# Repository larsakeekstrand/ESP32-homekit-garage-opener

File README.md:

# ESP32 Homekit garage door opener
## Introduction
This is a homekit garage opener for the ESP32. It's a bit a work in progress, but it should mostly work.

Features:
* Controls a relay that opens/closes the door.
* Uses a reed sensor to detect if the door is open/closed.
* Contains a DHT22 temperature/humidity sensor.
* Auto-close timer (default 10 min, configurable, 0 = off).
* Door-left-open HomeKit alert via a Contact Sensor accessory.
* Vacation/lockout switch to refuse all open and close commands.
* Local status and configuration web page at `http://<device-ip>:8080/`.

Schematics for the hardware are in [docs/Schematic_GarageOpener.pdf](docs/Schematic_GarageOpener.pdf), drawn in [KiCad](https://www.kicad.org/) — the project (rev 1 carrier PCB for an ESP32 DevKitC V4) is in [hardware/garage-opener-pcb](hardware/garage-opener-pcb), with a bill of materials in [docs/BOM_GarageOpener.pdf](docs/BOM_GarageOpener.pdf). The routed board ([render](docs/PCB_GarageOpener_3d.png)) and Aisler-ready Gerbers are in [hardware/garage-opener-pcb/fab](hardware/garage-opener-pcb/fab), and a 3D-printable wall-mounted enclosure for it is in [hardware/enclosure](hardware/enclosure/README.md).

The STL files below are for the original hand-wired prototype housing.

STL files for the housing can be found [here](https://github.com/larsakeekstrand/ESP32-homekit-garage-opener/blob/2dc0cb2f88ffee0f719a3f48c10d991301077dc2/docs/GarageOpenerTop.stl), [here](https://github.com/larsakeekstrand/ESP32-homekit-garage-opener/blob/2dc0cb2f88ffee0f719a3f48c10d991301077dc2/docs/GarageOpenerBottom.stl) and [here](https://github.com/larsakeekstrand/ESP32-homekit-garage-opener/blob/d89407ebe4e6d4afd1c8a517a600cc80013ba3aa/docs/GarageOpenerBottomButton.stl).

An overview of how to assemble the housing can be found [here](https://github.com/larsakeekstrand/ESP32-homekit-garage-opener/blob/d89407ebe4e6d4afd1c8a517a600cc80013ba3aa/docs/GarageOpenerCompleteNotPrintable.stl).

## Safety features

### Auto-close timer

When the door has been open for more than **10 minutes** (default), the firmware automatically
sends a close command. The timeout is configurable on the local web page (see below); set it to
`0` to disable auto-close entirely.

### Door-left-open alert

A HomeKit **Contact Sensor** named **"Garage Left Open"** fires when the door has been open for
more than **5 minutes** (default). Enable notifications on it in the Home app to receive an alert.
Set the threshold to `0` on the web page to disable the alert. The sensor still reports even when
the lockout switch is ON.

### Vacation / lockout switch

A HomeKit **Switch** named **"Lockout"** puts the opener into an absolute freeze: while it is ON,
HomeKit open and close commands are refused and the auto-close timer is suspended. It can be
toggled from both the Home app and the local web page — they stay in sync.

### Local status and configuration web page

The device serves a status and config page at `http://<device-ip>:8080/` on the local network (plain
HTTP, no HTTPS, LAN only). Port **8080** is used because the HomeKit (HAP) server already occupies
port 80. Find the device's IP from your router, or via mDNS — it advertises over Bonjour, e.g.
`dns-sd -B _hap._tcp` shows it as `GarageOpener-XXXXXX`.

**First-time setup — set a password promptly.** On the very first visit the device has no password
and shows a one-time "create password" screen (trust-on-first-use). Anyone on the same LAN can set
the password until you do, so set it immediately after first access. The firmware-flash endpoint
(`POST /api/ota`) is equally open during this window — since it can replace the running firmware,
set the password promptly, especially on an untrusted LAN (uploaded images are validated against the
`garage` app descriptor and the endpoint is LAN-only, but the credential gate is the main barrier).

After the password is set, the page requires **HTTP Basic Auth** (username `admin`, your chosen
password). From there you can:

* View live status: door state, lockout, Wi-Fi RSSI, temperature, humidity, uptime.
* View system info: firmware version, free heap, MAC address, IP address, reset reason.
* View persisted counters: door cycles, auto-closes, door-left-open trips, faults.
* Edit the auto-close timeout, door-left-open threshold, **OTA poll interval** (5–1440 min),
  **door-move timeout** (3–30 s), and **relay pulse length** (100–2000 ms). All settings persist
  in NVS. The OTA poll interval takes effect within ~10 s — no reboot needed.
* Trigger an immediate GitHub version check with **Check for updates now** (no effect while
  auto-updates are paused — resume first).
* Restart the device with **Reboot device** (asks for confirmation; HomeKit and the web page drop
  for ~15 s while it boots).
* Change the admin password.
* Reset a latched auto-close fault (see below).

**Editing the web page source.** The page HTML and JavaScript live in `tools/web/page.html`
(main status/config page) and `tools/web/setup.html` (first-time password setup). After editing
either file, regenerate the embedded C string literals:

```bash
python3 tools/gen_web_page.py
```

This rewrites the relevant sections of `main/web_server.c`. Rebuild and flash as normal.
Edit only `tools/web/*.html` — the `PAGE_HTML` / `SETUP_HTML` C strings in `web_server.c` are
generated and will be silently overwritten by the next `gen_web_page.py` run.

### Auto-close fault detection

If the reed sensor remains stuck reporting "open" after a close command, the firmware makes at most
**3 attempts** then latches auto-close off, so it never oscillates the door. A minimum of 60
seconds between pulses and a per-hour cap serve as additional backstops.

The fault is surfaced three ways:

1. A banner on the local web page with a **Reset** button to clear it manually.
2. A HomeKit **StatusFault** indicator on the Garage Door Opener accessory.
3. A log message at error severity.

The fault clears automatically when the door genuinely reports closed, or immediately when you
press **Reset** on the web page.

### HomeKit caveat after updating

If you are updating from a firmware version that does not include these features, you may need to
**remove and re-add the accessory** in the Home app to make the new **"Garage Left Open"** Contact
Sensor and **"Lockout"** Switch tiles visible.

## Getting started
### Setup host environment

Set up the host environment and **Espressif ESP-IDF v5.5.2** using the instructions given [here](https://docs.espressif.com/projects/esp-idf/en/latest/get-started/index.html).

Set up the Espressif esp-homekit-sdk using the instructions given [here](https://github.com/espressif/esp-homekit-sdk).

The DHT22/AM2301 driver is fetched automatically by the **ESP Component Manager** (declared in `main/idf_component.yml`) — no separate clone of `esp-idf-lib` is required.

### Get ESP32-homekit-garage-opener

Clone this repository **alongside** (not inside) your `~/esp/` directory:

```
cd ~/source    # ~/source is a sibling of ~/esp
git clone https://github.com/larsakeekstrand/ESP32-homekit-garage-opener
```

After the installation the directory structure should look like this:

```
~/
  esp/
    esp-idf            # ESP-IDF v5.5.2
    esp-homekit-sdk    # Espressif HomeKit SDK (cloned peer)
  source/
    ESP32-homekit-garage-opener   # this repo
```

`CMakeLists.txt` locates `esp-homekit-sdk` at `../../esp/esp-homekit-sdk` relative to the repo root, or via the `HOMEKIT_PATH` environment variable.

### Configure
Source the ESP-IDF environment, then run `idf.py menuconfig` to set Wi-Fi credentials and the HomeKit setup code before flashing:
```bash
. ~/esp/esp-idf/export.sh
cd ~/source/ESP32-homekit-garage-opener
idf.py menuconfig
```

Set the Wi-Fi SSID and password under **App Wi-Fi configuration**. Set the HomeKit setup code and ID under **HAP Setup** (or leave the hardcoded defaults for development).

### Compile and Flash

```bash
idf.py set-target esp32
idf.py build
idf.py flash monitor
```

## Continuous Integration & Releases

### CI (automatic)

Every push to `main` and every pull request targeting `main` triggers the **Build** workflow
(`.github/workflows/build.yml`). It:

- Builds the firmware with ESP-IDF v5.5.2 and target `esp32`.
- Verifies the image fits the 1600 KB OTA partition.
- Uploads `garage.bin` as a downloadable artifact.

Warnings in the app sources are treated as errors (`-Werror`), so a warning will fail the build.

### Cutting a release (manual)

1. Go to the **Actions** tab in GitHub.
2. Select the **Release** workflow.
3. Click **Run workflow**, enter a version string (e.g. `1.1.0`, no leading `v`), and confirm.

The workflow builds with that version baked in as `FW_VERSION`, tags the commit `v1.1.0`, and
publishes a GitHub Release with two assets: `garage.bin` and `version.txt`.

### Self-updating OTA

The device checks `releases/latest` on GitHub **every hour** (default). If `version.txt` reports a
version newer than the running firmware, the device downloads `garage.bin` via HTTPS and reboots
into the new image. A bad image that never completes initialization is **automatically rolled back**
by the bootloader.

The poll interval and repo base URL are configurable via `idf.py menuconfig` →
**Example Configuration** → OTA options (`CONFIG_OTA_POLL_INTERVAL_SEC`,
`CONFIG_OTA_GITHUB_BASE_URL`).

> **Security note:** anyone who can publish a GitHub Release to this repo can push firmware to the
> device. Images are not cryptographically signed — acceptable for a personal repo.

### LAN push-OTA (forced / beta updates)

You can push a locally-built image directly to the device over the local network — useful for
testing a beta build without cutting a GitHub release.

**Build a versioned beta first.** A build with the default `FW_VERSION=0.0.0-dev` is treated as
*older* than the latest release by the hourly poller, so it would be reverted on the next poll.
Pass a real version to avoid that:

```bash
idf.py -DFW_VERSION=1.2.0-beta build
```

**Upload with `garage-push`.** The CLI lives at `tools/garage-push/` (Rust). Build and run it with
`cargo`:

```bash
cd tools/garage-push
cargo build                            # or: cargo run -- <subcommand>
```

Subcommands:

| Subcommand | What it does |
|------------|-------------|
| `push --host <ip> --file build/garage.bin` | Uploads the image to the device, waits for it to reboot into the new firmware |
| `resume --host <ip>` | Re-enables the hourly GitHub auto-update poller |
| `status --host <ip>` | Prints the device status JSON |

The `push` subcommand authenticates with HTTP Basic Auth (username `admin`, your web page password).
The password is resolved in order: `--password <pw>` flag → `$GARAGE_PASSWORD` environment variable
→ interactive prompt.

The device validates the uploaded image before flashing: it checks the app descriptor for the
correct project name and magic word. A wrong or corrupt image is rejected and the running firmware
is untouched. An image that does boot but then crashes or hangs is **automatically rolled back** by
the bootloader (same rollback mechanism as GitHub OTA).

**Auto-update pause.** A successful `push` automatically pauses the hourly GitHub poller; the pause
flag is stored in NVS and survives reboots. Consequently, if the pushed beta fails to boot and the
bootloader rolls back to the previous image, that restored image comes back with auto-updates still
paused — run `garage-push resume --host <ip>` (or toggle the web-page **Auto-update** switch) to
re-enable them. Re-enable auto-updates with:

```bash
cargo run -- resume --host <ip>
```

Or toggle the **Auto-update** switch on the local web page — it shows **on** or **PAUSED**.

### Wi-Fi credentials & OTA

Wi-Fi credentials are stored in the **`nvs` flash partition**, which OTA never touches (OTA only
rewrites the inactive app slot). So **credentials persist across updates** — you don't re-enter them
when the device self-updates.

The release images built by CI are **provisioning-mode** (no credentials baked in). Don't put your
SSID/password into the build or into GitHub — provision the device instead:

- **First-time / after a reset:** when the device is unprovisioned it advertises a BLE service named
  `PROV_XXYYZZ` (last 3 bytes of its MAC) and prints a **QR code + proof-of-possession (POP)** to the
  serial monitor. Install Espressif's **ESP BLE Provisioning** app (iOS/Android), scan the QR code
  (or pick `PROV_XXYYZZ` and enter the POP), choose your Wi-Fi, and enter the password. The creds are
  saved to NVS over an encrypted BLE link.
- **Re-provision:** short-press the boot/reset button (~3 s) to reset the network → the device
  re-advertises for provisioning. A long press (~10 s) is a full factory reset (also unpairs
  HomeKit).

> A locally-built **hardcoded** image (`menuconfig` → App Wi-Fi → *Use hardcoded credentials*) is fine
> for bench testing, but the first OTA replaces it with a provisioning image. Because esp-wifi caches
> the hardcoded credentials in NVS, the provisioning image reconnects using them — but from then on
> the device is provisioning-based, so re-provision over BLE if you ever clear the network config.

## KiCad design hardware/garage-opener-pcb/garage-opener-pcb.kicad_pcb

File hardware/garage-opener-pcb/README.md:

# Garage opener carrier PCB (rev 1)

KiCad 10 project for a carrier board that an **ESP32 DevKitC V4 (ESP32-WROOM-32U, 38-pin)** plugs
into. It adds a 5 V screw-terminal input (PTC fuse + Schottky), an on-board SRD-05VDC relay for the
opener's push-button input, a protected reed-switch input, an on-board DHT22, RUN/DOOR LEDs and two
board-ID straps. The GPIO map is identical to the prototype (`main/board.h`), so the same firmware
and OTA image run on both.

- Schematic: `garage-opener-pcb.kicad_sch` (PDF: `../../docs/Schematic_GarageOpener.pdf`)
- BOM: `bom.csv` (DNP parts excluded); printable version `../../docs/BOM_GarageOpener.pdf`,
  regenerated with `python3 make_bom_pdf.py` after re-exporting `bom.csv`. U1 is the devkit itself; its footprint needs two
  1x19 2.54 mm female headers, which are not a separate BOM line.
- Design + bring-up checklist: `../../docs/superpowers/specs/2026-10-16-carrier-pcb-schematic-design.md`

## Checking the schematic after edits

    python3 check_schematic.py

Exports the netlist with `kicad-cli` and checks every net, footprint, the DNP ID straps, and that
each GPIO in `main/board.h` lands on the right circuit. Run ERC too:

    kicad-cli sch erc --severity-all garage-opener-pcb.kicad_sch

Expected: 0 errors; 1 warning that the embedded `MMBT2222A` differs from the library copy (it is a
flattened derived symbol) is harmless.

## Before ordering a PCB

- Measure the devkit: rows must be 25.4 mm apart (footprint `garage-opener:ESP32-DevKitC-V4_Socket`).
- Power J1 from a **5.1–5.2 V** supply: the Schottky + PTC drop ~0.45 V, and the devkit's LDO needs ~4.3 V.
- Check whether the devkit has a diode on USB VBUS before using USB and J1 at the same time.
- Board ID rev 1 = `00` (R9, R11 fitted). Future revisions: fit R8 and/or R10 instead.
- J1–J3 are pluggable Phoenix-style headers. J1 (power) is 3.81 mm pitch and J2/J3 are 5.08 mm, so the
  power plug can't go into the reed socket.
- Relay contacts follow KiCad's SRD symbol (J2: 1 COM, 2 NO, 3 NC). On the first board, confirm
  with a meter that COM–NO is open while the relay is unpowered.

## PCB

Renders: `kicad-cli pcb render --side top ...` and `--perspective --rotate '-40,0,30'`. KiCad's stock LED
model is red (the BOM has green RUN / amber DOOR), U2 shows as a socket (the DHT22 is soldered flat), and
the devkit has no 3D model.

- `garage-opener-pcb.kicad_pcb` is the source of truth. `tools/layout.py`, `tools/route.py` and
  `tools/silk.py` built rev 1 from scratch. Layout refuses to overwrite without `--force`, which
  discards the routing. `route.py --refill-only` refills the GND pours and adds stitching vias.
- Check after any edit: `python3 check_pcb.py`. It checks placement, connector/USB orientation and
  the silkscreen labels, that the custom rules in `garage-opener-pcb.kicad_dru` load, DRC, unconnected
  items and schematic parity.
- Fab files: `sh fab.sh`, then upload `fab/garage-opener-pcb-gerbers.zip` to Aisler (2 layers,
  1.6 mm, HASL). Aisler also accepts the `.kicad_pcb` directly. `fab/` also has a STEP model and an STL;
  the enclosure scripts read the STL.
- The DHT22 is soldered **flat** (leads bent 90°, grille facing the lid) over the marked keep-out,
  not in a socket.
- Relay contact tracks are 1 mm wide with 2 mm clearance to everything else (net class `Contact`).
- Enclosure: `../enclosure/` (generated from this board; rerun its `export_board_dims.py` after moving parts).

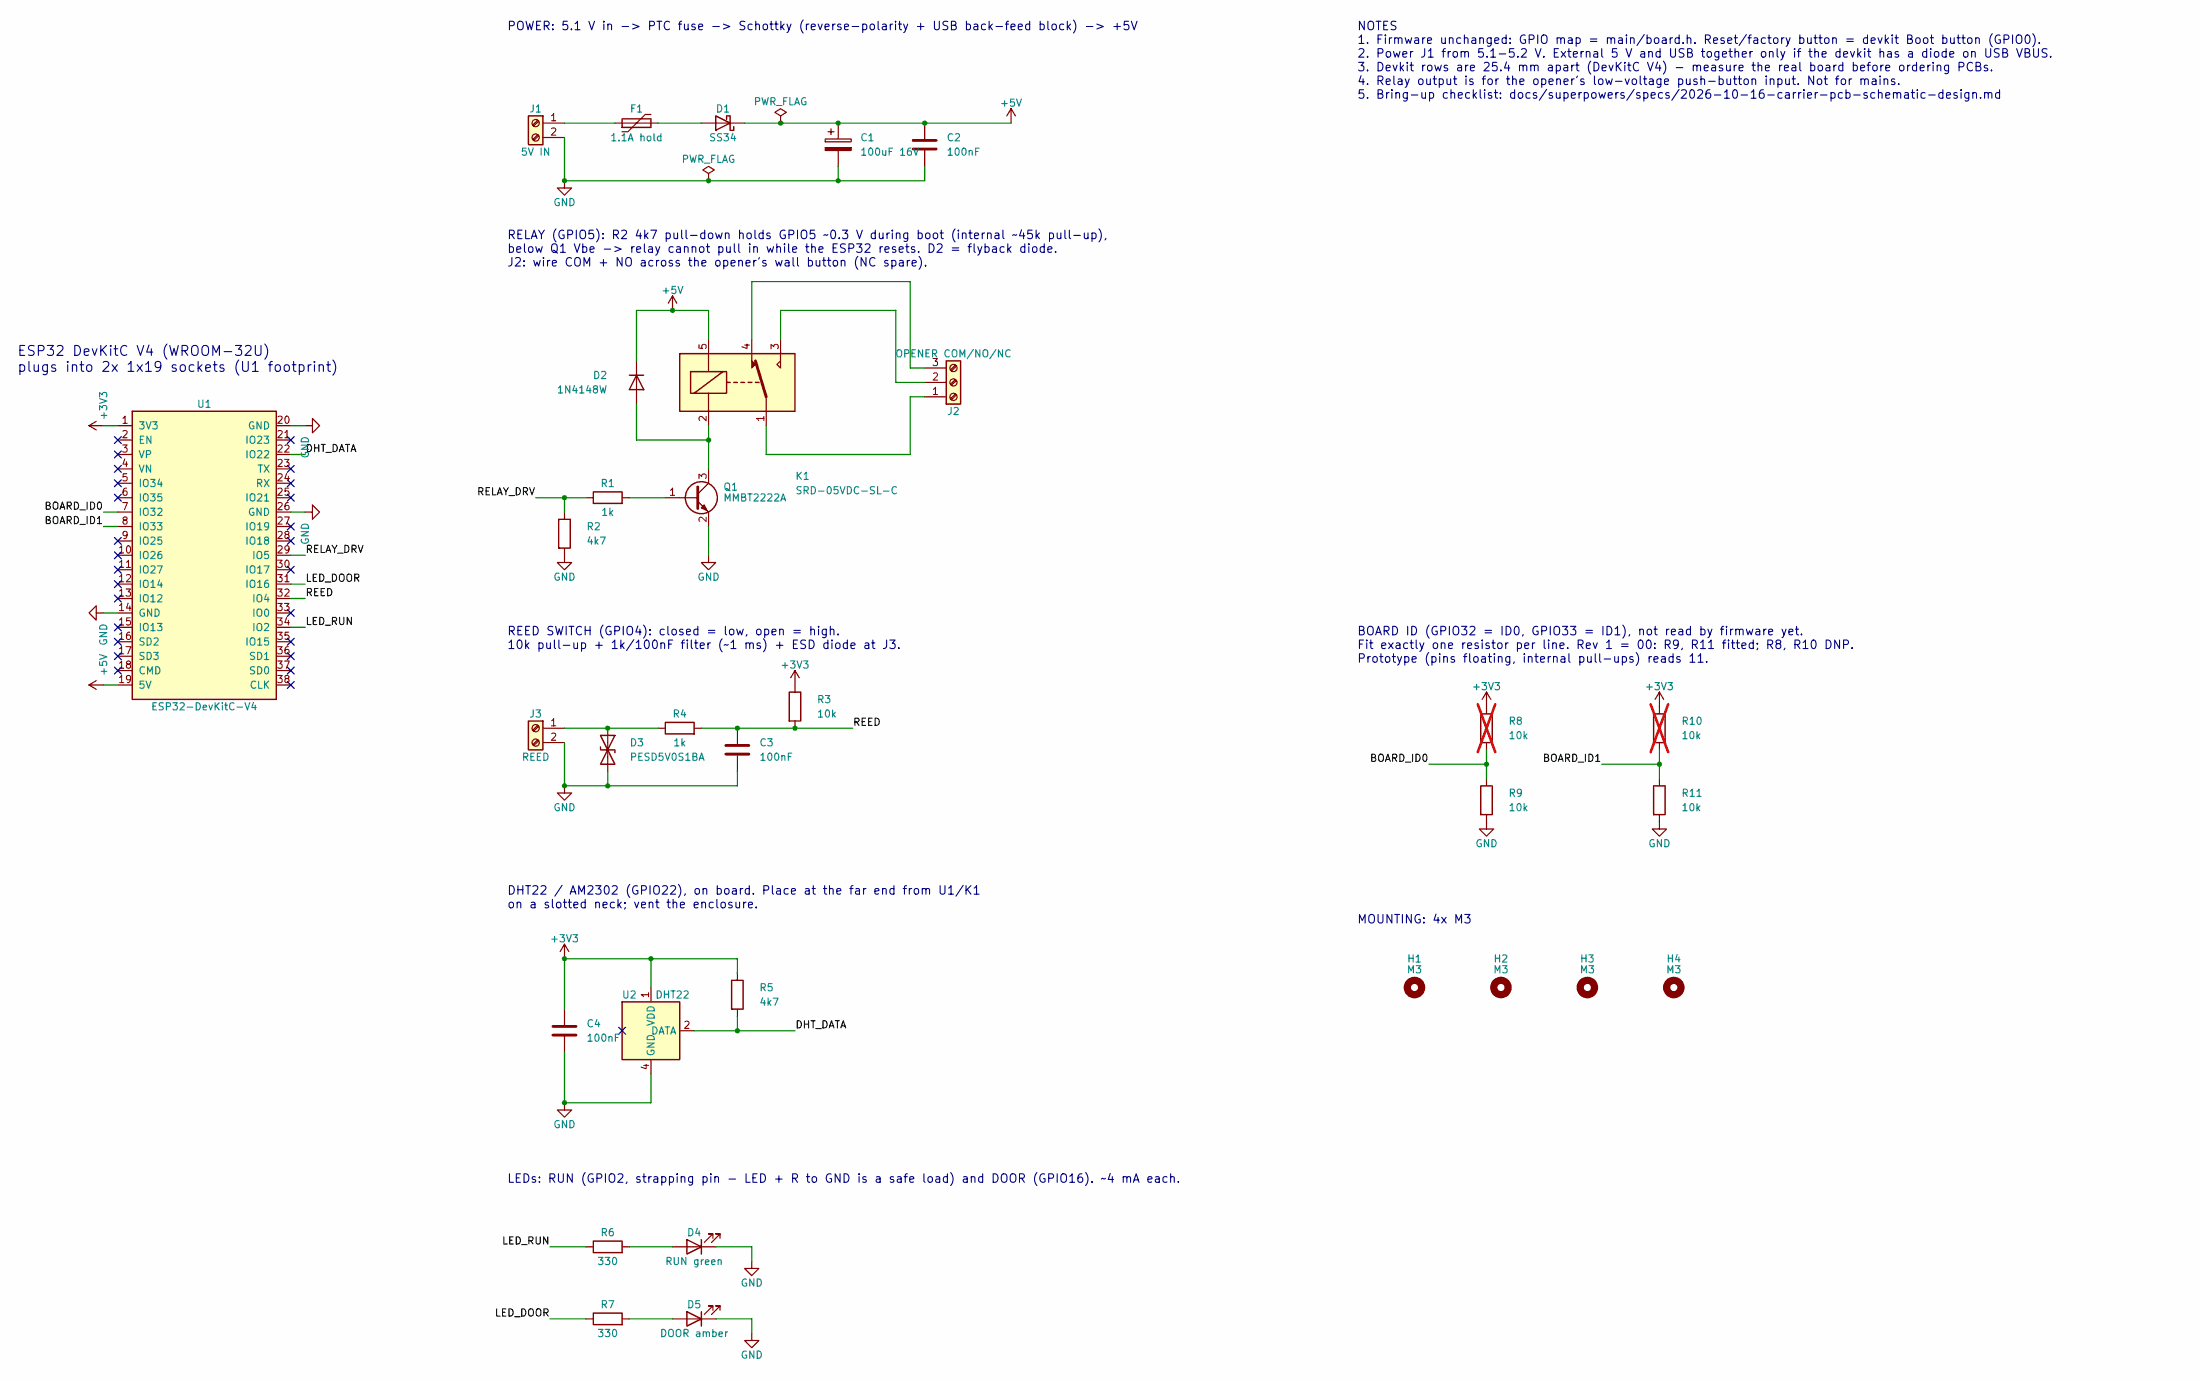
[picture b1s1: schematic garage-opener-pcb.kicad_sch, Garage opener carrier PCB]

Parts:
C1: 100uF 16V; CP_Radial_D6.3mm_P2.50mm
C2, C3, C4: 100nF; C_0805_2012Metric; LCSC C49678
D1: SS34; D_SMA; LCSC C8678
D2: 1N4148W; D_SOD-123; LCSC C81598
D3: PESD5V0S1BA; D_SOD-323
D4: RUN green; LED_D3.0mm
D5: DOOR amber; LED_D3.0mm
F1: 1.1A hold; Fuse_1812_4532Metric
H1, H2, H3, H4: M3; MountingHole_3.2mm_M3
J1: 5V IN; PhoenixContact_MC_1,5_2-G-3.81_1x02_P3.81mm_Horizontal
J2: OPENER COM/NO/NC; PhoenixContact_MSTBA_2,5_3-G-5,08_1x03_P5.08mm_Horizontal
J3: REED; PhoenixContact_MSTBA_2,5_2-G-5,08_1x02_P5.08mm_Horizontal
K1: SRD-05VDC-SL-C; Relay_SPDT_SANYOU_SRD_Series_Form_C; LCSC C35449
Q1: MMBT2222A; SOT-23
R1, R4: 1k; R_0805_2012Metric; LCSC C17513
R2, R5: 4k7; R_0805_2012Metric; LCSC C17673
R3, R9, R11: 10k; R_0805_2012Metric; LCSC C17414
R6, R7: 330; R_0805_2012Metric; LCSC C17630
R8, R10: 10k; R_0805_2012Metric; LCSC C17414; not fitted
U1: ESP32-DevKitC-V4; ESP32-DevKitC-V4_Socket
U2: DHT22; PinSocket_1x04_P2.54mm_Vertical

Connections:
+3V3: C4.1, R3.1, R5.1, R8.1, R10.1, U1.1 (3V3), U2.1 (VDD)
+5V: C1.1, C2.1, D1.1 (K), D2.1 (K), K1.5, U1.19 (5V)
/BOARD_ID0: R8.2, R9.1, U1.7 (IO32)
/BOARD_ID1: R10.2, R11.1, U1.8 (IO33)
/DHT_DATA: R5.2, U1.22 (IO22), U2.2 (DATA)
/LED_DOOR: R7.1, U1.31 (IO16)
/LED_RUN: R6.1, U1.34 (IO2)
/REED: C3.1, R3.2, R4.2, U1.32 (IO4)
/RELAY_DRV: R1.1, R2.1, U1.29 (IO5)
GND: C1.2, C2.2, C3.2, C4.2, D3.2 (A2), D4.1 (K), D5.1 (K), J1.2, J3.2, Q1.2 (E), R2.2, R9.2, R11.2, U1.14 (GND), U1.20 (GND), U1.26 (GND), U2.4 (GND)
unnamed: D1.2 (A), F1.2
unnamed: D2.2 (A), K1.2, Q1.3 (C)
unnamed: D3.1 (A1), J3.1, R4.1
unnamed: D4.2 (A), R6.2
unnamed: D5.2 (A), R7.2
unnamed: F1.1, J1.1
unnamed: J2.1, K1.1
unnamed: J2.2, K1.3
unnamed: J2.3, K1.4
unnamed: Q1.1 (B), R1.2

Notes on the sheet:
BOARD ID (GPIO32 = ID0, GPIO33 = ID1), not read by firmware yet. Fit exactly one resistor per line. Rev 1 = 00: R9, R11 fitted; R8, R10 DNP. Prototype (pins floating, internal pull-ups) reads 11.
LEDs: RUN (GPIO2, strapping pin - LED + R to GND is a safe load) and DOOR (GPIO16). ~4 mA each.
DHT22 / AM2302 (GPIO22), on board. Place at the far end from U1/K1 on a slotted neck; vent the enclosure.
REED SWITCH (GPIO4): closed = low, open = high. 10k pull-up + 1k/100nF filter (~1 ms) + ESD diode at J3.
ESP32 DevKitC V4 (WROOM-32U) plugs into 2x 1x19 sockets (U1 footprint)
MOUNTING: 4x M3
NOTES 1. Firmware unchanged: GPIO map = main/board.h. Reset/factory button = devkit Boot button (GPIO0). 2. Power J1 from 5.1-5.2 V. External 5 V and USB together only if the devkit has a diode on USB VBUS. 3. Devkit rows are 25.4 mm apart (DevKitC V4) - measure the real board before ordering PCBs.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
RELAY (GPIO5): R2 4k7 pull-down holds GPIO5 ~0.3 V during boot (internal ~45k pull-up), below Q1 Vbe -> relay cannot pull in while the ESP32 resets. D2 = flyback diode. J2: wire COM + NO across the opener's wall button (NC spare).
POWER: 5.1 V in -> PTC fuse -> Schottky (reverse-polarity + USB back-feed block) -> +5V

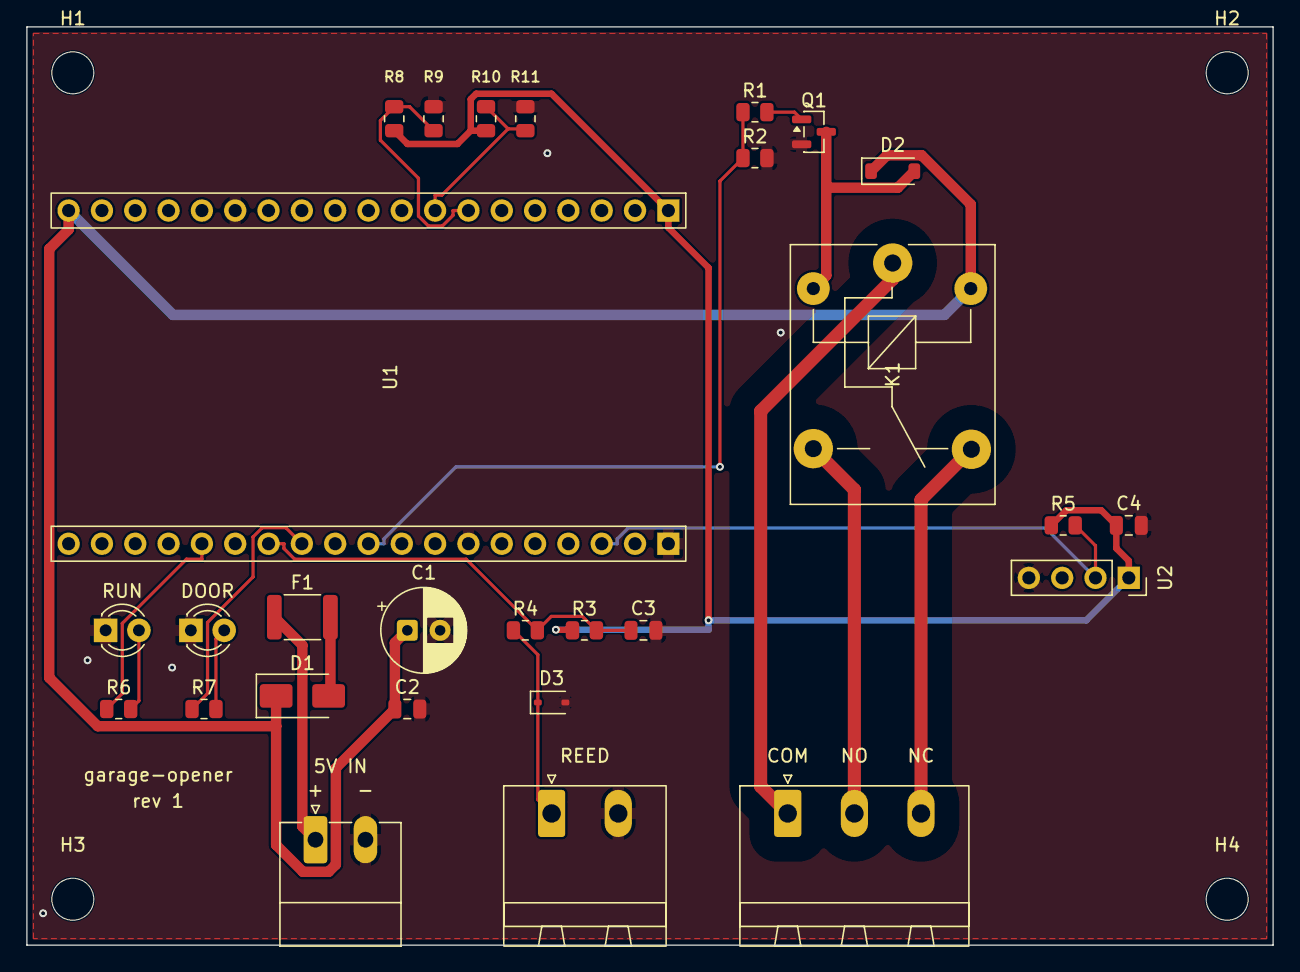
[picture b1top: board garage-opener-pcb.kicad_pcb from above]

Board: 2 copper layers, 95.0 x 70.0 mm, 32 parts (0 on the bottom side), 20 nets.

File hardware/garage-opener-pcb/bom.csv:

"Refs","Value","Footprint","LCSC","Qty"
"C1","100uF 16V","Capacitor_THT:CP_Radial_D6.3mm_P2.50mm","","1"
"C2-C4","100nF","Capacitor_SMD:C_0805_2012Metric","C49678","3"
"D1","SS34","Diode_SMD:D_SMA","C8678","1"
"D2","1N4148W","Diode_SMD:D_SOD-123","C81598","1"
"D3","PESD5V0S1BA","Diode_SMD:D_SOD-323","","1"
"D4","RUN green","LED_THT:LED_D3.0mm","","1"
"D5","DOOR amber","LED_THT:LED_D3.0mm","","1"
"F1","1.1A hold","Fuse:Fuse_1812_4532Metric","","1"
"J1","5V IN","Connector_Phoenix_MC:PhoenixContact_MC_1,5_2-G-3.81_1x02_P3.81mm_Horizontal","","1"
"J2","OPENER COM/NO/NC","Connector_Phoenix_MSTB:PhoenixContact_MSTBA_2,5_3-G-5,08_1x03_P5.08mm_Horizontal","","1"
"J3","REED","Connector_Phoenix_MSTB:PhoenixContact_MSTBA_2,5_2-G-5,08_1x02_P5.08mm_Horizontal","","1"
"K1","SRD-05VDC-SL-C","Relay_THT:Relay_SPDT_SANYOU_SRD_Series_Form_C","C35449","1"
"Q1","MMBT2222A","Package_TO_SOT_SMD:SOT-23","","1"
"R1,R4","1k","Resistor_SMD:R_0805_2012Metric","C17513","2"
"R2,R5","4k7","Resistor_SMD:R_0805_2012Metric","C17673","2"
"R3,R9,R11","10k","Resistor_SMD:R_0805_2012Metric","C17414","3"
"R6,R7","330","Resistor_SMD:R_0805_2012Metric","C17630","2"
"U1","ESP32-DevKitC-V4","garage-opener:ESP32-DevKitC-V4_Socket","","1"
"U2","DHT22","Connector_PinSocket_2.54mm:PinSocket_1x04_P2.54mm_Vertical","","1"

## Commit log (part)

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2021-07-20 Added new readme
2021-07-20 Added support for DHT temp and humidity sensor
2021-07-20 Added schematics
2021-07-20 Added stl files
2021-07-20 Updated readme with stl files
2021-07-20 Added STL files for buttons
2021-07-20 Added more stl files
